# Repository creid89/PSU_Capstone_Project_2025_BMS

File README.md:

2025 PSU Senior Capstone Project

Battery Management System for PSU Student EPL (Engineering Prototyping Lab)

Members:
Cuauhtemoc Gomez Angeles <cuauh@pdx.edu>
Cody Reid <codreid@pdx.edu>
Fernando Custodio Calderon <fernan27@pdx.edu>
Tyler Tran <tytran@pdx.edu>
Daniel Anishchenko <danish2@pdx.edu>

Inudstry Sponsor: 
Edward Ivory <edivory@pdx.edu>

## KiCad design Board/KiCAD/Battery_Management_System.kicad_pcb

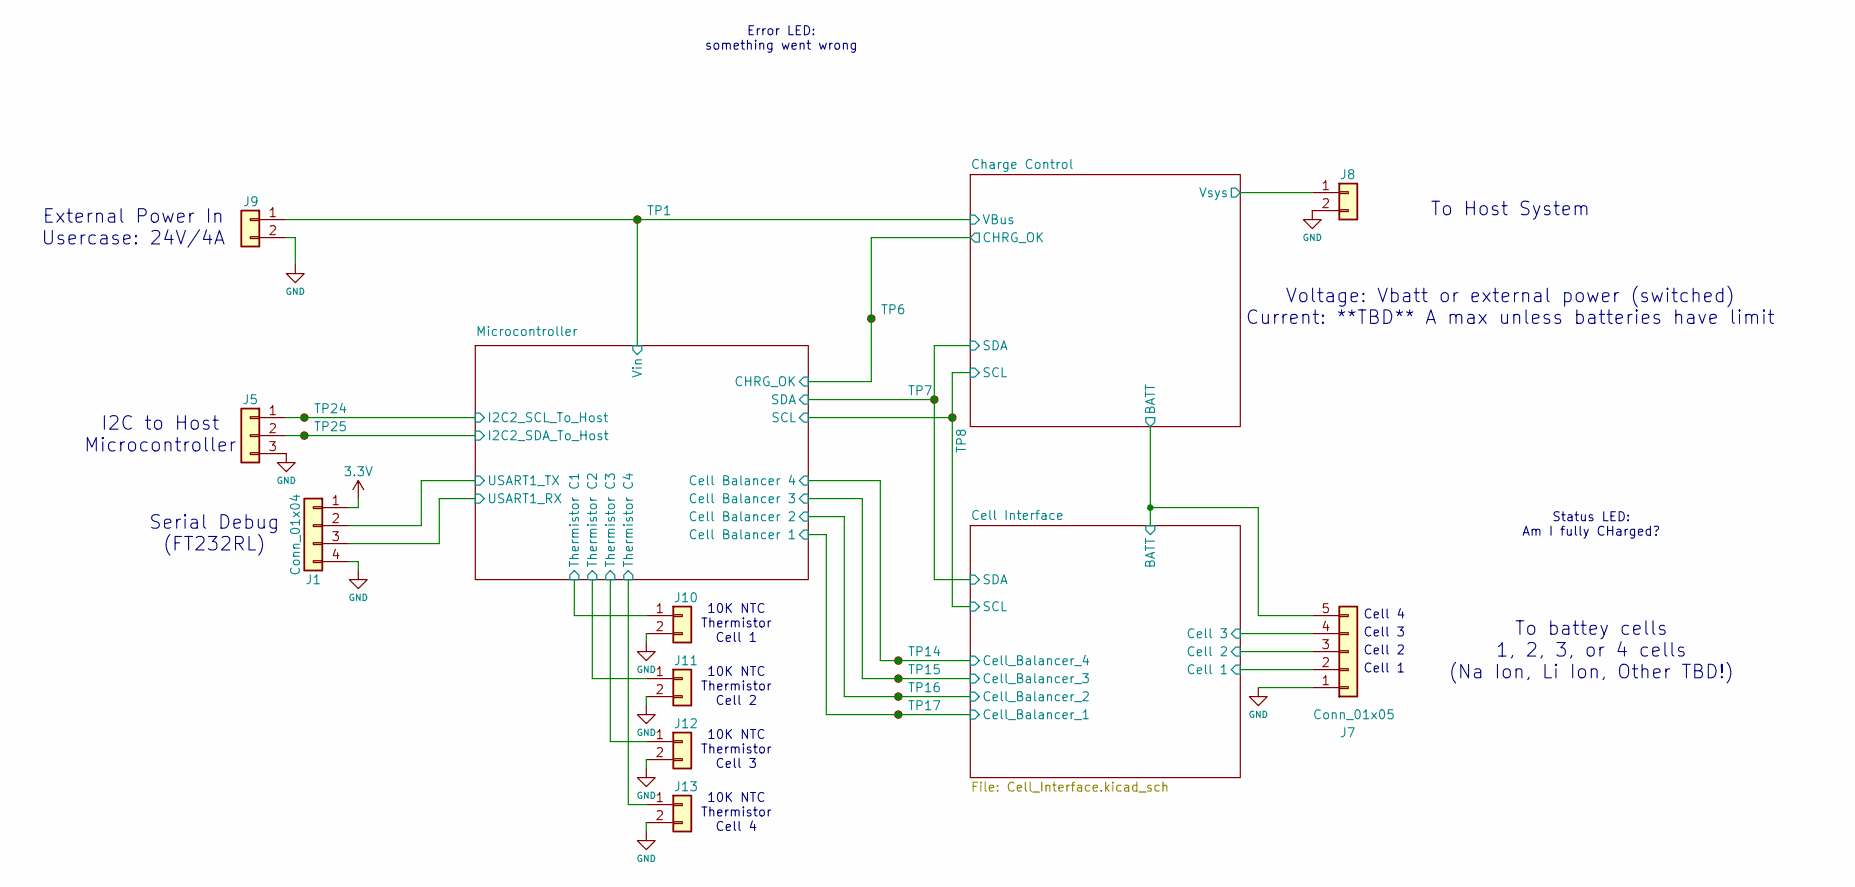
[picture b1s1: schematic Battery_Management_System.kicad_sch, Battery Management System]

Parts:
J1: Conn_01x04; PinHeader_1x04_P2.54mm_Vertical
J5: Conn_01x03; PinHeader_1x03_P2.54mm_Vertical; MPN 732-5316-ND
J7: Conn_01x05; PinHeader_1x05_P2.54mm_Vertical; MPN 732-5318-ND
J8, J9, J10, J11, J12, J13: Conn_01x02; PinHeader_1x02_P2.54mm_Vertical; MPN 5-146285-2-ND
TP1, TP6, TP7, TP8, TP14, TP15, TP16, TP17, TP24, TP25: TestPoint_Small; TestPoint_Pad_1.0x1.0mm

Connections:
3.3V: J1.1; also elsewhere on the board
/Cell Interface/BATT: J7.5; also elsewhere on the board
/Cell Interface/Cell 1: J7.2; also elsewhere on the board
/Cell Interface/Cell 2: J7.3; also elsewhere on the board
/Cell Interface/Cell 3: J7.4; also elsewhere on the board
/Cell Interface/Cell_Balancer_1: TP17.1; also elsewhere on the board
/Cell Interface/Cell_Balancer_2: TP16.1; also elsewhere on the board
/Cell Interface/Cell_Balancer_3: TP15.1; also elsewhere on the board
/Cell Interface/Cell_Balancer_4: TP14.1; also elsewhere on the board
/Cell Interface/SCL: TP8.1; also elsewhere on the board
/Cell Interface/SDA: TP7.1; also elsewhere on the board
/Charge Control/CHRG_OK: TP6.1; also elsewhere on the board
/Charge Control/VBus: J9.1, TP1.1; also elsewhere on the board
/Charge Control/Vsys: J8.1; also elsewhere on the board
/Microcontroller/I2C2_SCL_To_Host: J5.1, TP24.1; also elsewhere on the board
/Microcontroller/I2C2_SDA_To_Host: J5.2, TP25.1; also elsewhere on the board
/Microcontroller/Thermistor C1: J10.1; also elsewhere on the board
/Microcontroller/Thermistor C2: J11.1; also elsewhere on the board
/Microcontroller/Thermistor C3: J12.1; also elsewhere on the board
/Microcontroller/Thermistor C4: J13.1; also elsewhere on the board
/Microcontroller/USART1_RX: J1.3; also elsewhere on the board
/Microcontroller/USART1_TX: J1.2; also elsewhere on the board
GND: J1.4, J5.3, J7.1, J8.2, J9.2, J10.2, J11.2, J12.2, J13.2; also elsewhere on the board

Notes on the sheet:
Cell 3
I2C to Host Microcontroller
10K NTC Thermistor Cell 1
Cell 4
10K NTC Thermistor Cell 3
10K NTC Thermistor Cell 2
Error LED: something went wrong
To battey cells 1, 2, 3, or 4 cells (Na Ion, Li Ion, Other TBD!)
Cell 2
To Host System Voltage: Vbatt or external power (switched) Current: **TBD** A max unless batteries have limit
Serial Debug (FT232RL)
External Power In Usercase: 24V/4A
Cell 1
Status LED: Am I fully CHarged?
10K NTC Thermistor Cell 4

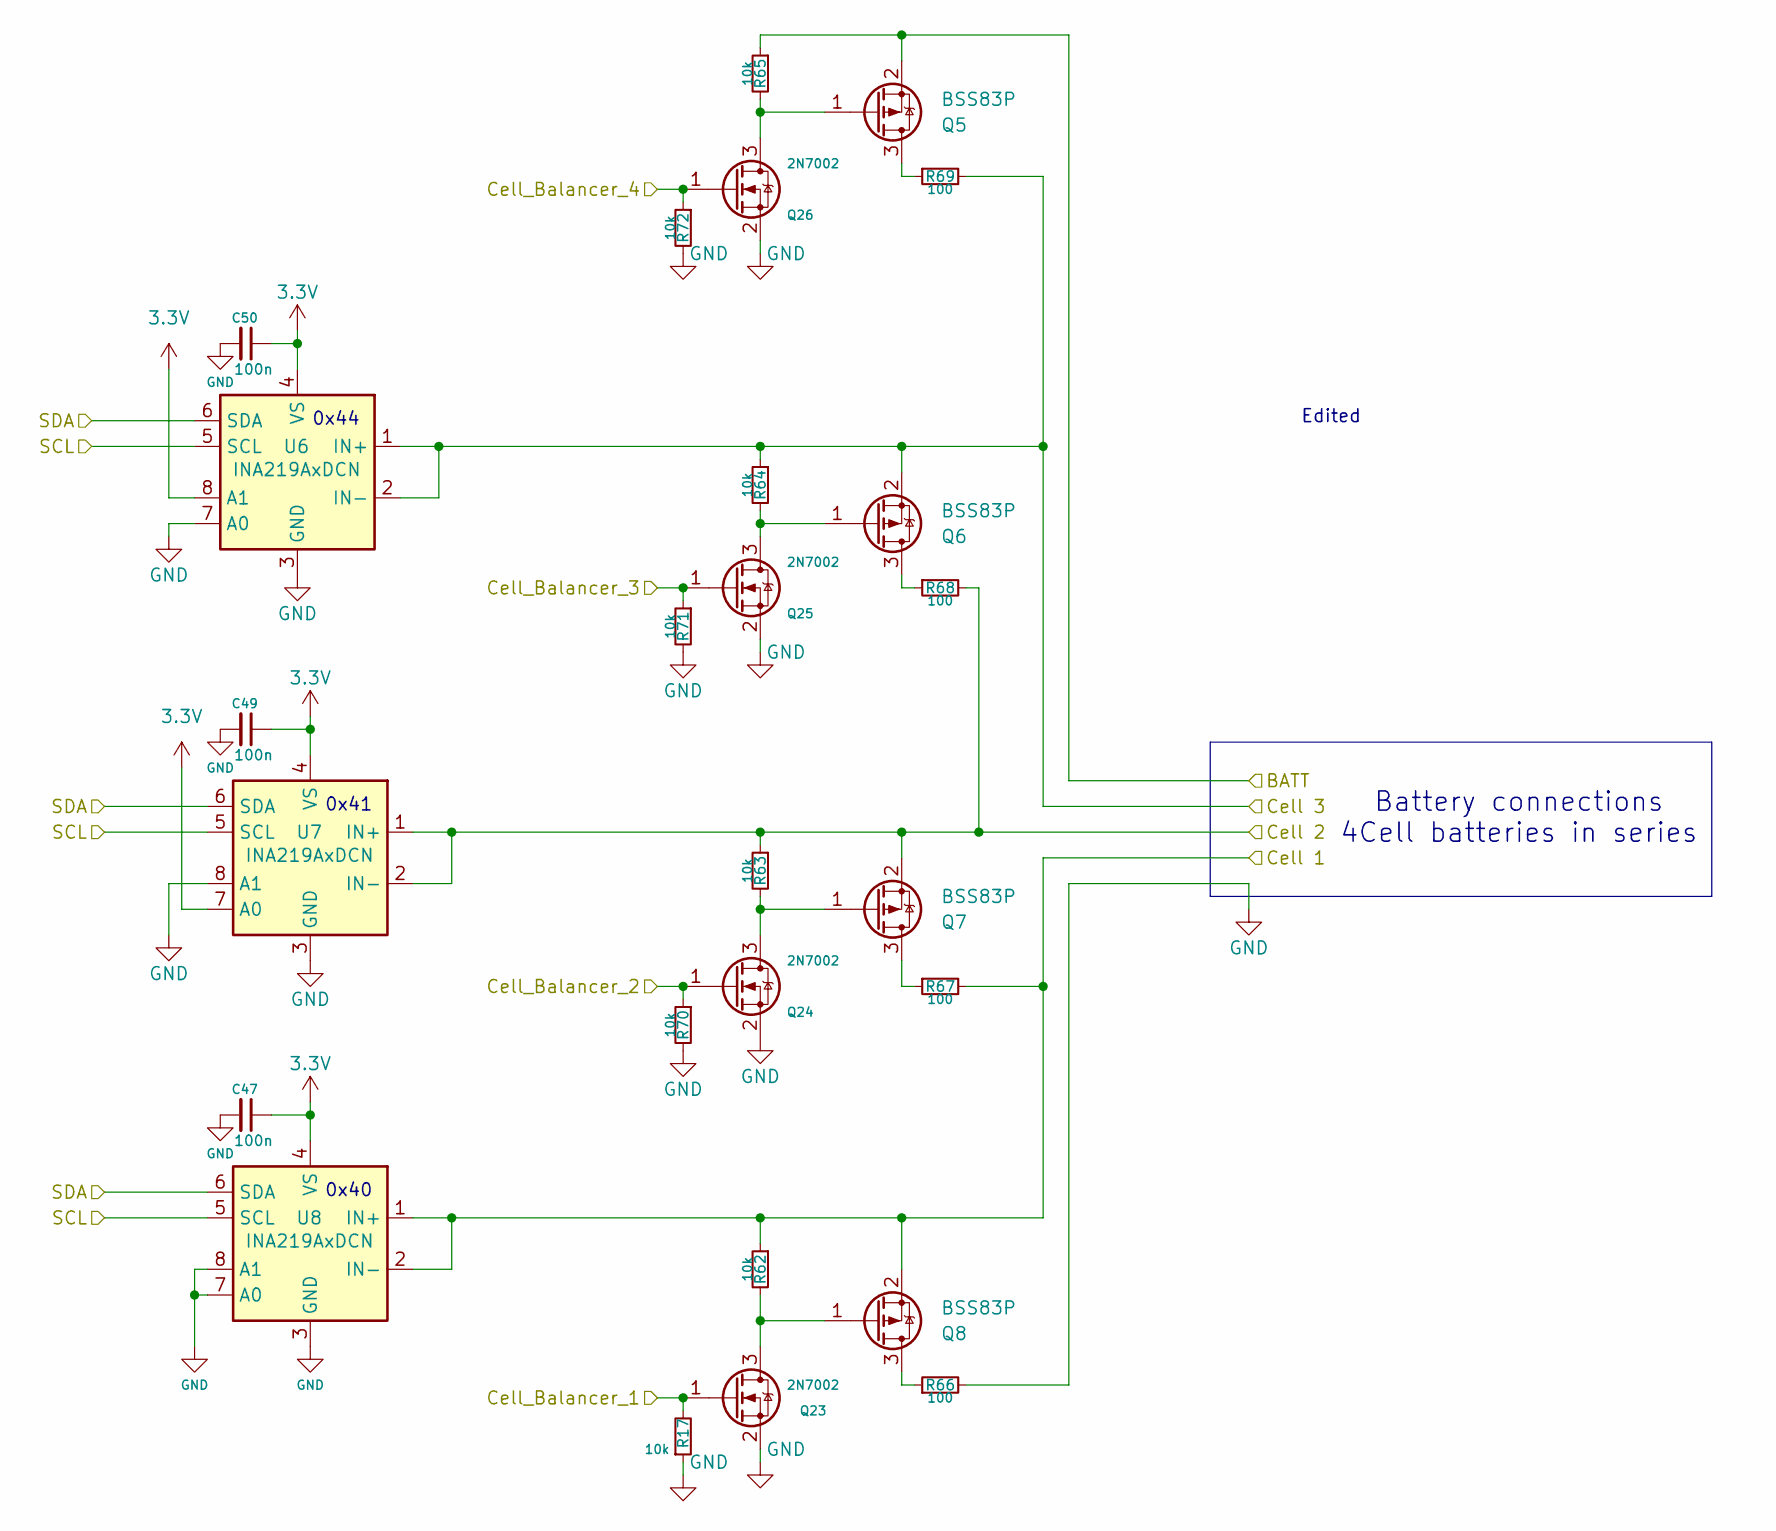
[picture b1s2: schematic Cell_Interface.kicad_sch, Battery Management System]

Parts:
C47, C49, C50: 100n; C_0603_1608Metric; MPN 1276-6720-1-ND
Q5, Q6, Q7, Q8: BSS83P; SOT-23; MPN BSS83PH6327XTSA1CT-ND
Q23, Q24, Q25, Q26: 2N7002; SOT-23; MPN 2N7002NCT-ND
R17, R62, R63, R64, R65, R70, R71, R72: 10k; R_0603_1608Metric; MPN RMCF0603FT10K0CT-ND
R66, R67, R68, R69: 100; R_1206_3216Metric; MPN RNCF1206TKY100RCT-ND
U6, U7, U8: INA219AxDCN; SOT-23-8; MPN 296-23770-1-ND

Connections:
3.3V: C47.1, C49.1, C50.1, U6.4 (VS), U6.8 (A1), U7.4 (VS), U7.7 (A0), U8.4 (VS); also elsewhere on the board
/Cell Interface/BATT: Q5.2 (S), R65.1; also elsewhere on the board
/Cell Interface/Cell 1: Q8.2 (S), R62.1, R67.2, U8.1 (IN+), U8.2 (IN-); also elsewhere on the board
/Cell Interface/Cell 2: Q7.2 (S), R63.1, R68.2, U7.1 (IN+), U7.2 (IN-); also elsewhere on the board
/Cell Interface/Cell 3: Q6.2 (S), R64.1, R69.2, U6.1 (IN+), U6.2 (IN-); also elsewhere on the board
/Cell Interface/Cell_Balancer_1: Q23.1 (G), R17.2; also elsewhere on the board
/Cell Interface/Cell_Balancer_2: Q24.1 (G), R70.1; also elsewhere on the board
/Cell Interface/Cell_Balancer_3: Q25.1 (G), R71.1; also elsewhere on the board
/Cell Interface/Cell_Balancer_4: Q26.1 (G), R72.1; also elsewhere on the board
/Cell Interface/SCL: U6.5 (SCL), U7.5 (SCL), U8.5 (SCL); also elsewhere on the board
/Cell Interface/SDA: U6.6 (SDA), U7.6 (SDA), U8.6 (SDA); also elsewhere on the board
GND: C47.2, C49.2, C50.2, Q23.2 (S), Q24.2 (S), Q25.2 (S), Q26.2 (S), R17.1, R66.2, R70.2, R71.2, R72.2, U6.3 (GND), U6.7 (A0), U7.3 (GND), U7.8 (A1), U8.3 (GND), U8.7 (A0), U8.8 (A1); also elsewhere on the board
unnamed: Q5.3 (D), R69.1
unnamed: Q6.3 (D), R68.1
unnamed: Q7.3 (D), R67.1
unnamed: Q8.3 (D), R66.1
unnamed: Q8.1 (G), Q23.3 (D), R62.2
unnamed: Q7.1 (G), Q24.3 (D), R63.2
unnamed: Q6.1 (G), Q25.3 (D), R64.2
unnamed: Q5.1 (G), Q26.3 (D), R65.2

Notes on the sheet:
0x44
Battery connections 4Cell batteries in series
Edited
0x40
0x41

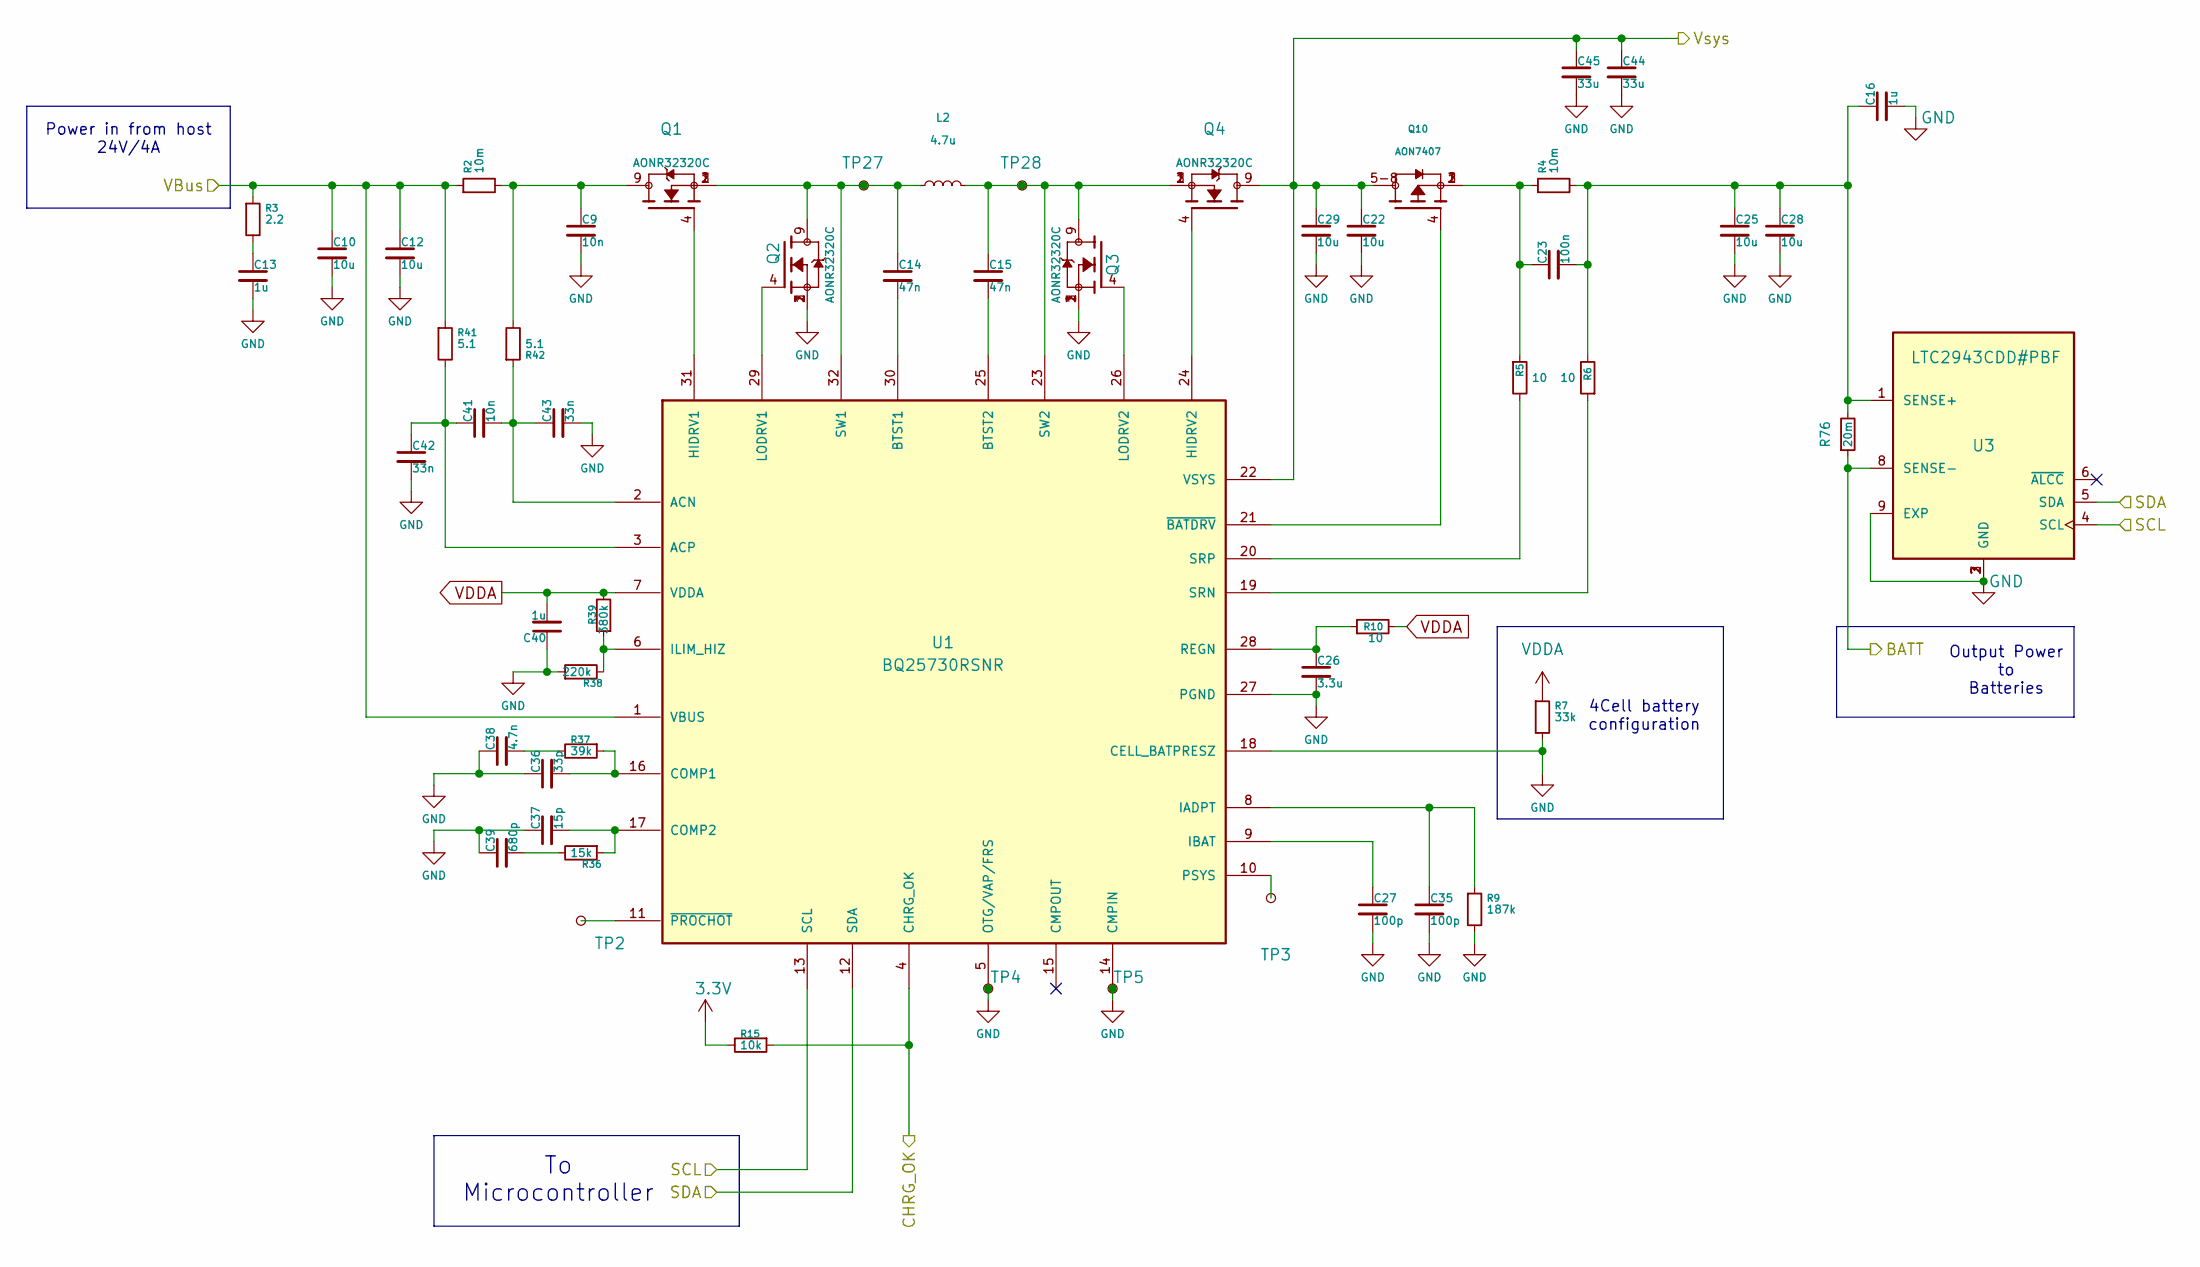
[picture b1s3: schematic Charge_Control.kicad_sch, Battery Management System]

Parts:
C9, C41: 10n; C_0603_1608Metric; MPN 490-3194-1-ND
C10, C12, C22, C25, C28, C29: 10u; C_1206_3216Metric; MPN 1276-1804-1-ND
C13, C16, C40: 1u; C_0603_1608Metric; MPN 1276-1946-1-ND
C14, C15: 47n; C_0603_1608Metric; MPN 490-4934-1-ND
C23: 100n; C_0603_1608Metric; MPN 1276-6720-1-ND
C26: 3.3u; C_0603_1608Metric; MPN 1276-1892-1-ND
C27, C35: 100p; C_0603_1608Metric; MPN 490-1427-1-ND
C36: 33p; C_0603_1608Metric; MPN 490-1415-1-ND
C37: 15p; C_0603_1608Metric; MPN 478-600S150JT250XT4KCT-ND
C38: 4.7n; C_0603_1608Metric; MPN 445-6912-1-ND
C39: 680p; C_0603_1608Metric; MPN 399-C0603C681F5GACTUCT-ND
C42, C43: 33n; C_0603_1608Metric; MPN 490-8025-1-ND
C44, C45: 33u; C_1206_3216Metric; MPN 490-1415-1-ND
L2: 4.7u; L_10.4x10.4_H4.8; MPN 495-1805-1-ND
Q1, Q2, Q3, Q4: AONR32320C; TRANS_AON7408; MPN 785-AONR32320CCT-ND
Q10: AON7407; TRANS_AON7407; MPN 785-1306-1-ND
R2, R4: 10m; R_1206_3216Metric; MPN CSR1206FK10L0CT-ND
R3: 2.2; R_1206_3216Metric
R5, R6, R10: 10; R_0603_1608Metric; MPN RMCF0603FT10R0CT-ND
R7: 33k; R_0603_1608Metric; MPN RMCF0603FT33K0CT-ND
R9: 187k; R_0603_1608Metric; MPN RMCF0603FT187KCT-ND
R15: 10k; R_0603_1608Metric; MPN RMCF0603FT10K0CT-ND
R36: 15k; R_0603_1608Metric; MPN RMCF0603FT15K0CT-ND
R37: 39k; R_0603_1608Metric; MPN RMCF0603JT39K0CT-ND
R38: 220k; R_0603_1608Metric; MPN RMCF0603FT220KCT-ND
R39: 380k; R_0603_1608Metric; MPN RMCF0603FT383KCT-ND
R41, R42: 5.1; R_0603_1608Metric; MPN RMCF0603FT5R10CT-ND
R76: 20m; R_1206_3216Metric; MPN CSR1206FK20L0CT-ND
TP2, TP3, TP4, TP5, TP27, TP28: TestPoint_Small; TestPoint_Pad_1.0x1.0mm
U1: BQ25730RSNR; IC_BQ25730RSNR; MPN BQ25730RSNR
U3: LTC2943CDD#PBF; MLF-8-1EP_3x3mm_P0.65mm_EP1.55x2.3mm; MPN LTC2943CDD#PBF

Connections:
3.3V: R15.2; also elsewhere on the board
/Cell Interface/BATT: R76.1, U3.8 (SENSE-); also elsewhere on the board
/Cell Interface/SCL: U1.13 (SCL), U3.4 (SCL); also elsewhere on the board
/Cell Interface/SDA: U1.12 (SDA), U3.5 (SDA); also elsewhere on the board
/Charge Control/CHRG_OK: R15.1, U1.4 (CHRG_OK); also elsewhere on the board
/Charge Control/VBus: C10.1, C12.1, R2.1, R3.1, R41.1, U1.1 (VBUS); also elsewhere on the board
/Charge Control/Vsys: C22.1, C29.1, C44.1, C45.1, Q4.9, Q10.5-8, U1.22 (VSYS); also elsewhere on the board
GND: C9.2, C10.2, C12.2, C13.2, C16.2, C22.2, C25.2, C26.2, C27.2, C28.2, C29.2, C35.2, C36.1, C37.1, C38.1, C39.1, C40.1, C42.2, C43.2, C44.2, C45.2, Q2.1, Q2.2, Q2.3, Q3.1, Q3.2, Q3.3, R7.2, R9.2, R38.1, TP4.1, TP5.1, U1.5 (OTG/VAP/FRS), U1.14 (CMPIN), U1.18 (CELL_BATPRESZ), U1.27 (PGND), U1.33, U1.34, U1.35, U1.36, U1.37, U1.38, U1.39, U1.40, U1.41, U1.42, U3.2 (GND), U3.3 (GND), U3.7 (GND), U3.9 (EXP); also elsewhere on the board
unnamed: C9.1, Q1.9, R2.2, R42.2
unnamed: C13.1, R3.2
unnamed: C23.1, Q10.1, Q10.2, Q10.3, R4.1, R5.1
unnamed: C38.2, R37.2
unnamed: C39.2, R36.2
unnamed: C41.2, C43.1, R42.1, U1.2 (ACN)
unnamed: C41.1, C42.1, R41.2, U1.3 (ACP)
unnamed: C14.2, U1.30 (BTST1)
unnamed: C15.2, U1.25 (BTST2)
unnamed: C36.2, R37.1, U1.16 (COMP1)
unnamed: C37.2, R36.1, U1.17 (COMP2)
unnamed: Q1.4, U1.31 (HIDRV1)
unnamed: Q4.4, U1.24 (HIDRV2)
unnamed: C35.1, R9.1, U1.8 (IADPT)
unnamed: C27.1, U1.9 (IBAT)
unnamed: R38.2, R39.1, U1.6 (ILIM_HIZ)
unnamed: Q2.4, U1.29 (LODRV1)
unnamed: Q3.4, U1.26 (LODRV2)
unnamed: TP3.1, U1.10 (PSYS)
unnamed: C26.1, R10.1, U1.28 (REGN)
unnamed: R6.1, U1.19 (SRN)
unnamed: R5.2, U1.20 (SRP)
unnamed: C14.1, L2.1, Q1.1, Q1.2, Q1.3, Q2.9, TP27.1, U1.32 (SW1)
unnamed: C15.1, L2.2, Q3.9, Q4.1, Q4.2, Q4.3, TP28.1, U1.23 (SW2)
unnamed: Q10.4, U1.21 (~BATDRV)
unnamed: TP2.1, U1.11 (~PROCHOT)
unnamed: C16.1, C23.2, C25.1, C28.1, R4.2, R6.2, R76.2, U3.1 (SENSE+)
VDDA: C40.2, R7.1, R10.2, R39.2, U1.7 (VDDA)

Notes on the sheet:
4Cell battery configuration
To Microcontroller
Power in from host 24V/4A
Output Power to Batteries

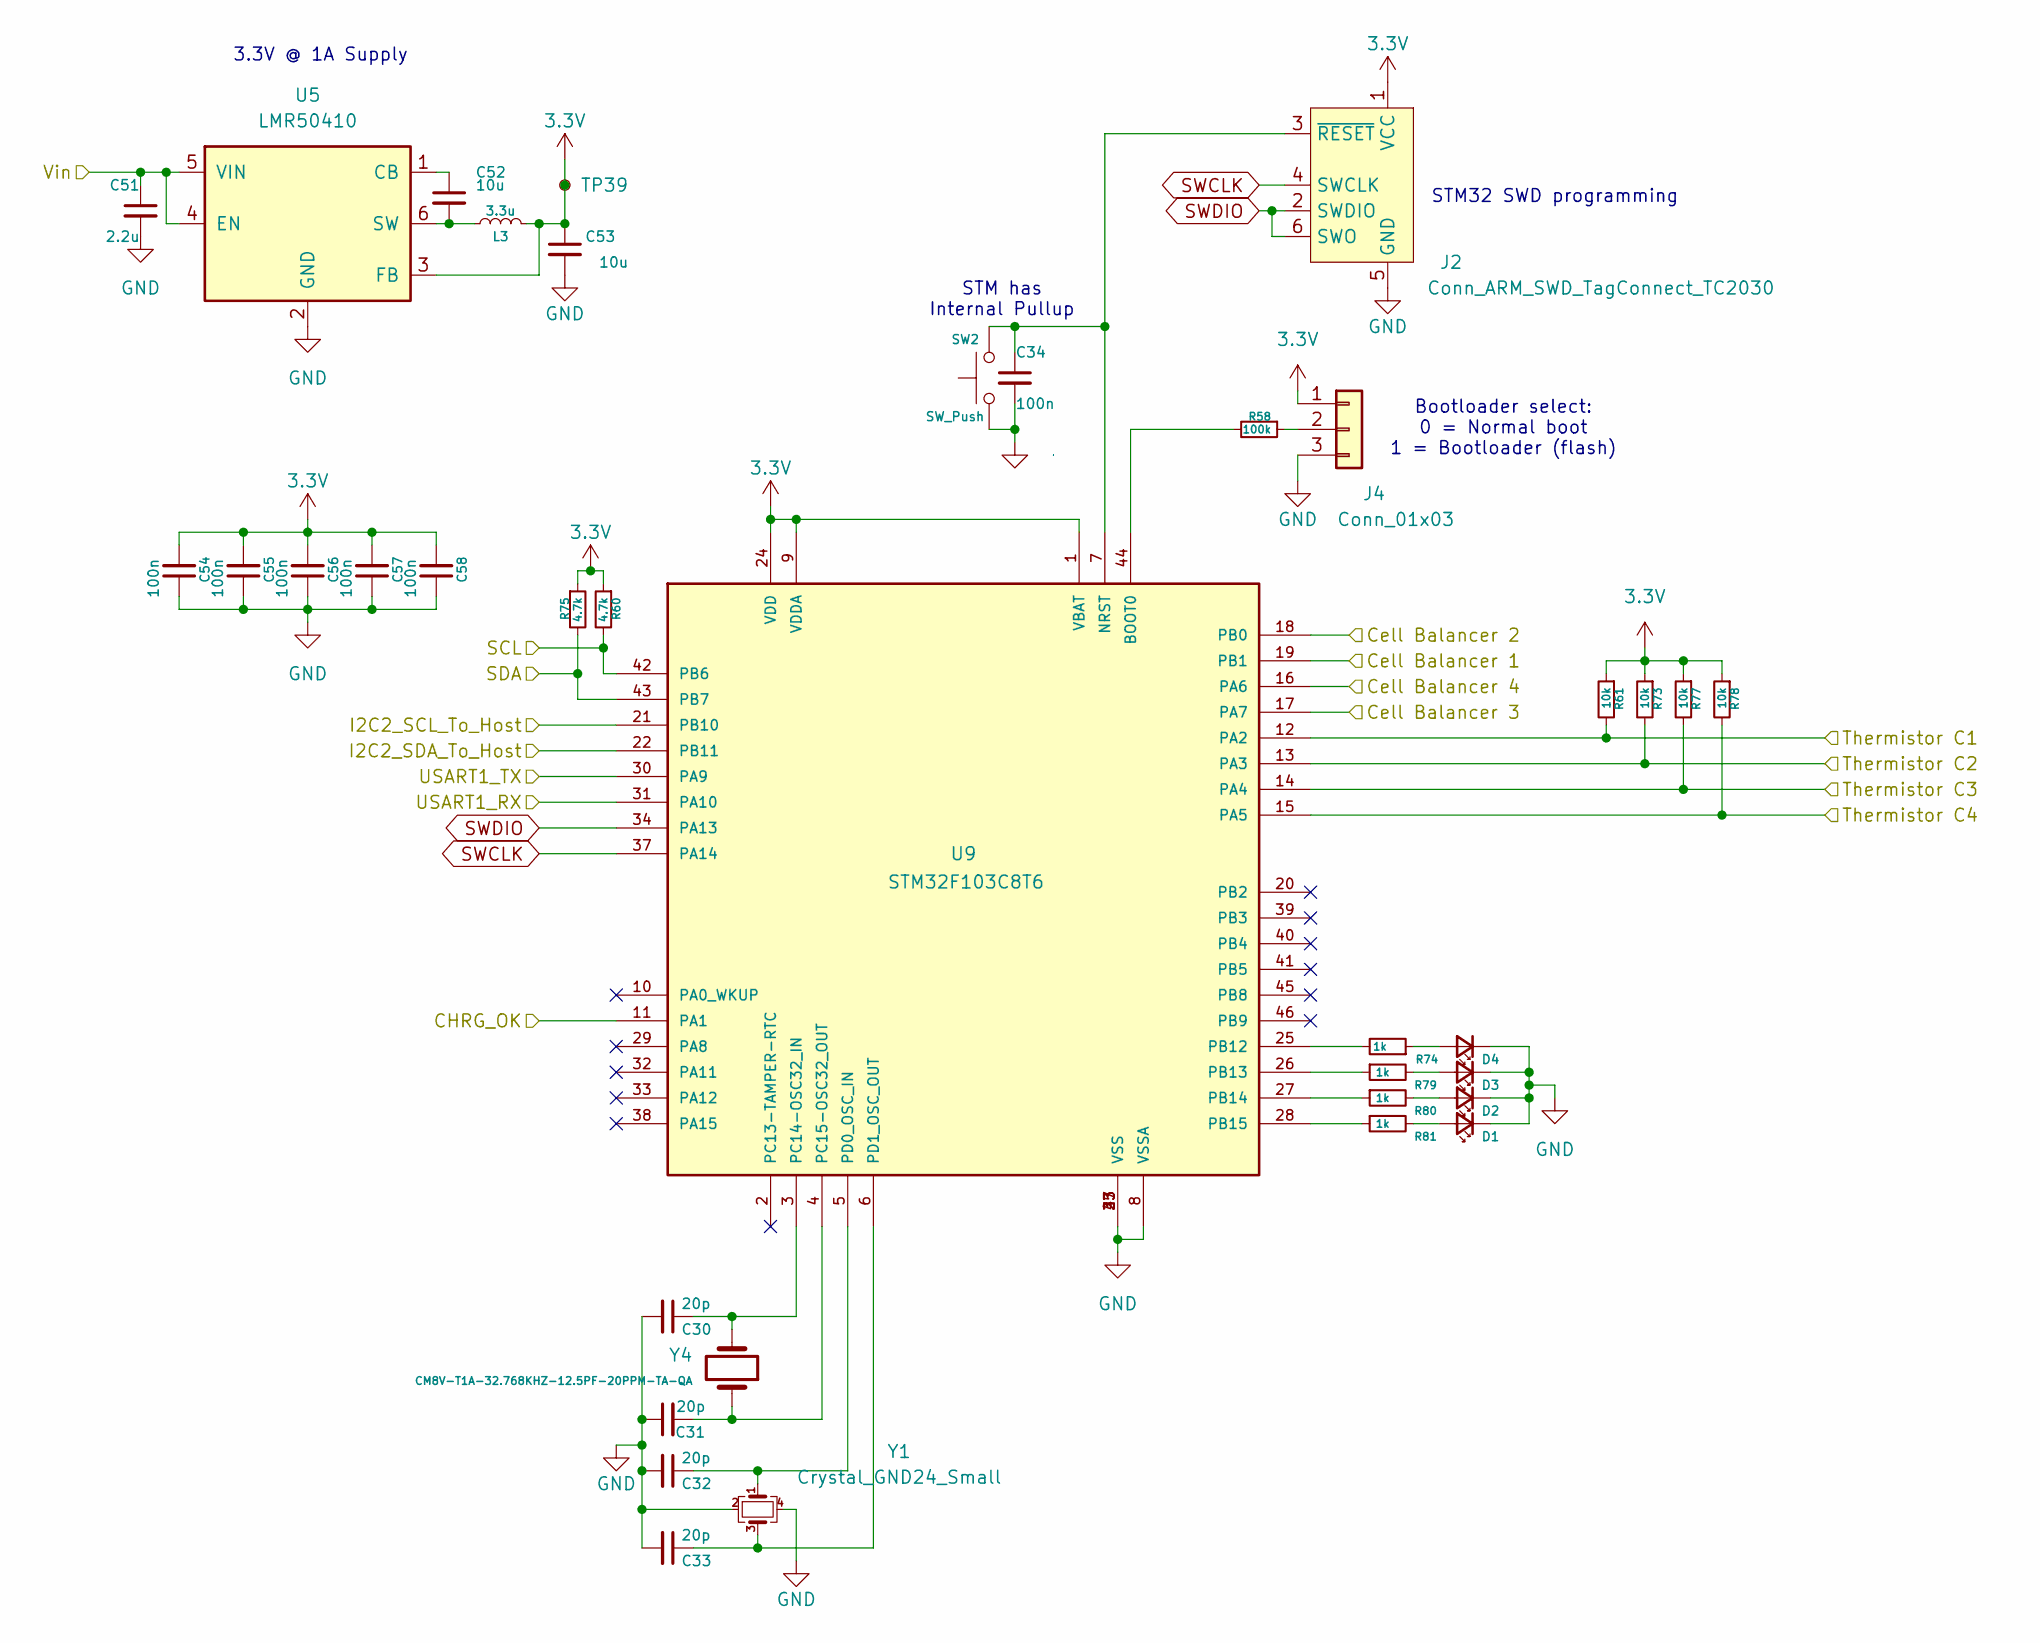
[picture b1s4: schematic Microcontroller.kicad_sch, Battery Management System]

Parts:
C30, C31, C32, C33: 20p; C_0603_1608Metric; MPN 478-600S200FT250XT4KCT-ND
C34, C54, C55, C56, C57, C58: 100n; C_0603_1608Metric; MPN 1276-6720-1-ND
C51: 2.2u; C_1206_3216Metric; MPN 587-2909-1-ND
C52, C53: 10u; C_1206_3216Metric; MPN 1276-1804-1-ND
D1, D2, D3, D4: LED_Small; LED_0603_1608Metric
J2: Conn_ARM_SWD_TagConnect_TC2030; Tag-Connect_TC2030-IDC-NL_2x03_P1.27mm_Vertical; MPN TC2030-CTX-ND
J4: Conn_01x03; PinHeader_1x03_P2.54mm_Vertical; MPN 732-5316-ND
L3: 3.3u; L_1008_2520Metric_Pad1.43x2.20mm_HandSolder; MPN 587-3227-1-ND
R58: 100k; R_0603_1608Metric; MPN RMCF0603FT100KCT-ND
R60, R75: 4.7k; R_0603_1608Metric; MPN RMCF0603FT4K70CT-ND
R61, R73, R77, R78: 10k; R_0603_1608Metric; MPN RMCF0603FT10K0CT-ND
R74, R79, R80, R81: 1k; R_0603_1608Metric; MPN RMCF0603FT10K0CT-ND
SW2: SW_Push; SW_Push_SPST_NO_Alps_SKRK; MPN CKN12220-1-ND
TP39: TestPoint_Small; TestPoint_Pad_1.0x1.0mm
U5: LMR50410; SOT-23-6; MPN 296-LMR50410XFDBVRCT-ND
U9: STM32F103C8T6; QFP50P900X900X160-48N; MPN STM32F103C8T6
Y1: Crystal_GND24_Small; Crystal_SMD_TXC_7M-4Pin_3.2x2.5mm; MPN 7V-8.000MDDQ-T
Y4: CM8V-T1A-32.768KHZ-12.5PF-20PPM-TA-QA; XTAL_CM8V-T1A-32.768KHZ-12.5PF-20PPM-TA-QA; MPN CM8V-T1A-32.768KHZ-12.5PF-20PPM-TA-QA

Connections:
3.3V: C53.1, C54.2, C55.2, C56.2, C57.2, C58.2, J2.1 (VCC), J4.1, L3.2, R60.1, R61.1, R73.1, R75.1, R77.1, R78.1, TP39.1, U5.3 (FB), U9.1 (VBAT), U9.9 (VDDA), U9.24 (VDD), U9.36 (VDD), U9.48 (VDD); also elsewhere on the board
/Cell Interface/Cell_Balancer_1: U9.19 (PB1); also elsewhere on the board
/Cell Interface/Cell_Balancer_2: U9.18 (PB0); also elsewhere on the board
/Cell Interface/Cell_Balancer_3: U9.17 (PA7); also elsewhere on the board
/Cell Interface/Cell_Balancer_4: U9.16 (PA6); also elsewhere on the board
/Cell Interface/SCL: R60.2, U9.42 (PB6); also elsewhere on the board
/Cell Interface/SDA: R75.2, U9.43 (PB7); also elsewhere on the board
/Charge Control/CHRG_OK: U9.11 (PA1); also elsewhere on the board
/Charge Control/VBus: C51.1, U5.4 (EN), U5.5 (VIN); also elsewhere on the board
/Microcontroller/I2C2_SCL_To_Host: U9.21 (PB10); also elsewhere on the board
/Microcontroller/I2C2_SDA_To_Host: U9.22 (PB11); also elsewhere on the board
/Microcontroller/Thermistor C1: R61.2, U9.12 (PA2); also elsewhere on the board
/Microcontroller/Thermistor C2: R73.2, U9.13 (PA3); also elsewhere on the board
/Microcontroller/Thermistor C3: R77.2, U9.14 (PA4); also elsewhere on the board
/Microcontroller/Thermistor C4: R78.2, U9.15 (PA5); also elsewhere on the board
/Microcontroller/USART1_RX: U9.31 (PA10); also elsewhere on the board
/Microcontroller/USART1_TX: U9.30 (PA9); also elsewhere on the board
GND: C30.2, C31.1, C32.2, C33.2, C34.2, C51.2, C53.2, C54.1, C55.1, C56.1, C57.1, C58.1, D1.1 (K), D2.1 (K), D3.1 (K), D4.1 (K), J2.5 (GND), J4.3, SW2.1, U5.2 (GND), U9.8 (VSSA), U9.23 (VSS), U9.35 (VSS), U9.47 (VSS), Y1.2, Y1.4; also elsewhere on the board
unnamed: D1.2 (A), R81.2
unnamed: D2.2 (A), R80.2
unnamed: D3.2 (A), R79.2
unnamed: D4.2 (A), R74.1
unnamed: C34.1, J2.3 (~RESET), SW2.2, U9.7 (NRST)
unnamed: J4.2, R58.1
unnamed: C52.1, U5.1 (CB)
unnamed: C52.2, L3.1, U5.6 (SW)
unnamed: R58.2, U9.44 (BOOT0)
unnamed: R74.2, U9.25 (PB12)
unnamed: R79.1, U9.26 (PB13)
unnamed: R80.1, U9.27 (PB14)
unnamed: R81.1, U9.28 (PB15)
unnamed: C30.1, U9.3 (PC14-OSC32_IN), Y4.2
unnamed: C31.2, U9.4 (PC15-OSC32_OUT), Y4.1
unnamed: C32.1, U9.5 (PD0_OSC_IN), Y1.1
unnamed: C33.1, U9.6 (PD1_OSC_OUT), Y1.3
SWCLK: J2.4 (SWCLK), U9.37 (PA14)
SWDIO: J2.2 (SWDIO), J2.6 (SWO), U9.34 (PA13)

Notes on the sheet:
STM32 SWD programming
3.3V @ 1A Supply
Bootloader select: 0 = Normal boot 1 = Bootloader (flash)
STM has Internal Pullup

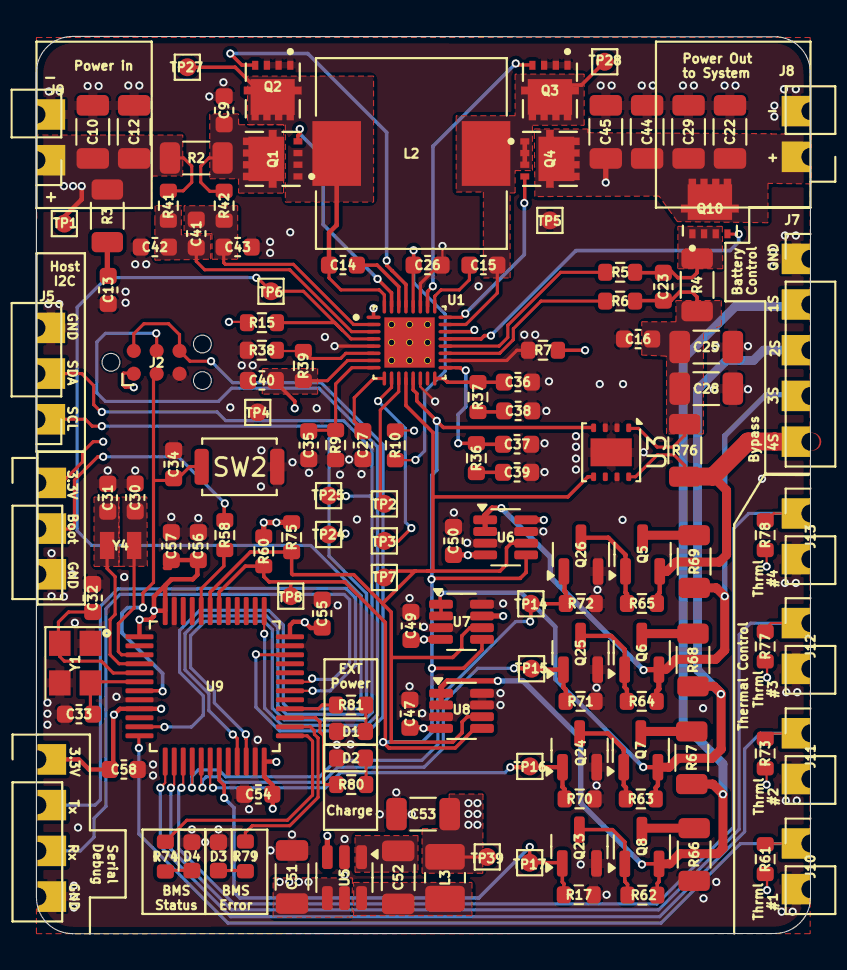
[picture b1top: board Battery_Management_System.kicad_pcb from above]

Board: 4 copper layers, 43.0 x 49.8 mm, 137 parts (0 on the bottom side), 78 nets.

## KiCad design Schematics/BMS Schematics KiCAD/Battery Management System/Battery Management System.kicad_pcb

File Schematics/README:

This folder contains the schematic designs and associated files for the hardware or electronics project. These schematics are essential for understanding the circuit design and the layout of the project.

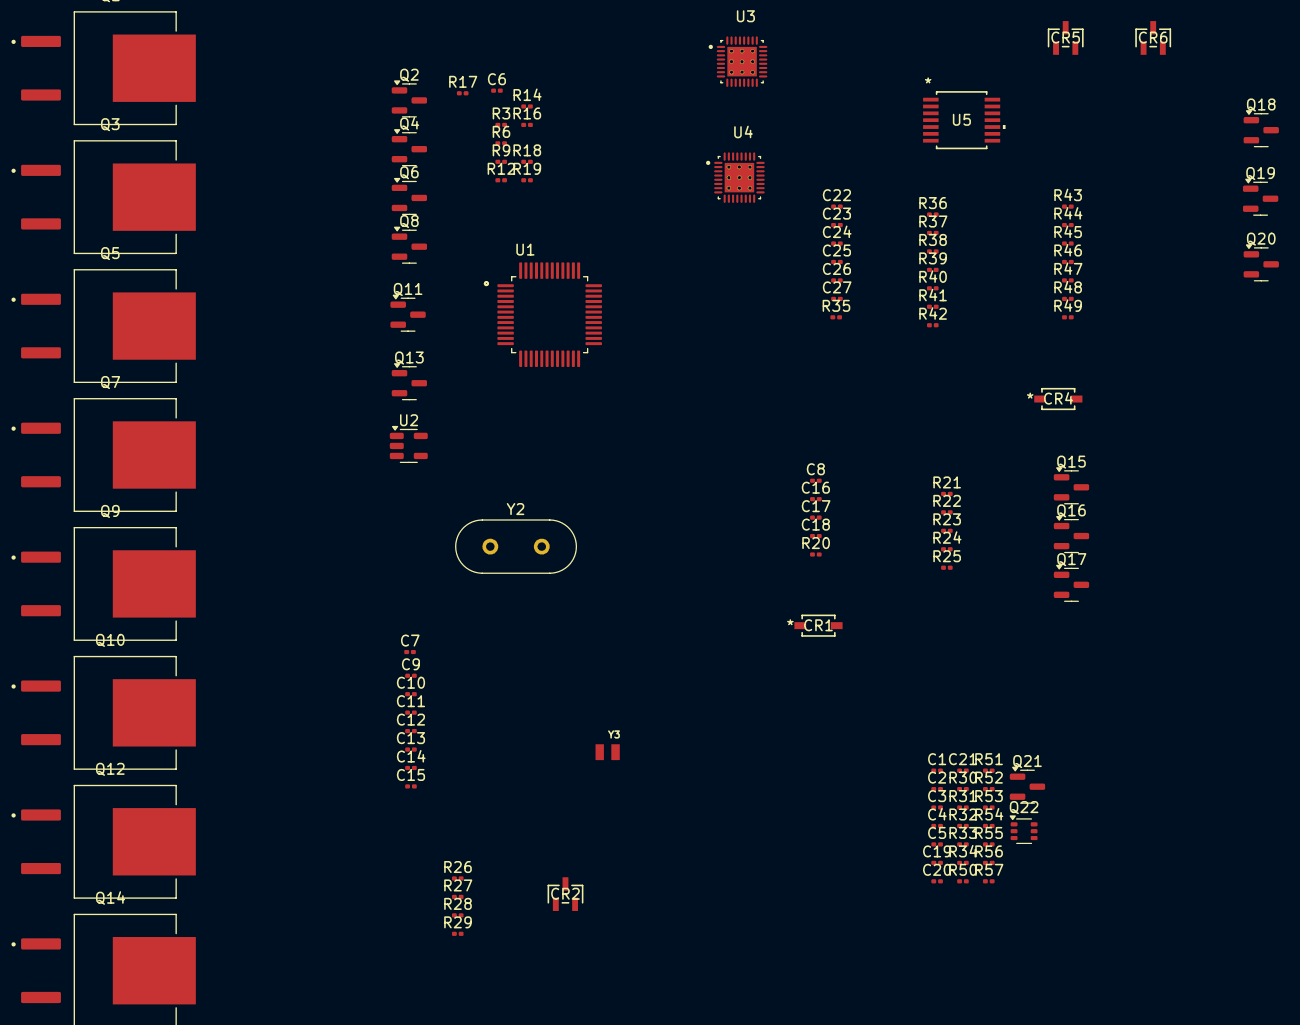
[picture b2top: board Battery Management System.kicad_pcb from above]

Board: 2 copper layers, 108 parts (0 on the bottom side), 78 nets, no tracks yet.

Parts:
C1, C2, C3, C4, C5, C8, C17, C18, C21: C; R_0201_0603Metric
C6, C7, C22, C23, C24: 1uF; C_0201_0603Metric
C9: 22nF; C_0201_0603Metric
C10: 10uF; C_0201_0603Metric
C11, C25, C26, C27: 0.1uF; C_0201_0603Metric
C12, C13, C14, C15: 20pF; C_0201_0603Metric
C16: C; C_0201_0603Metric
C19: 33p; R_0201_0603Metric
C20: 15p; R_0201_0603Metric
CR1, CR4: BZT52C5V6T-7; ZDO_SOD123_DIO
CR2, CR5, CR6: AZ23C5V6-7-F; DIODE3_AZ23C5V6-7-F_DIO
Q1, Q3, Q5, Q7, Q9, Q10, Q12, Q14: IRF9540NSTRLPBF; DPAK254P1524X483-4_3N
Q2, Q4, Q6, Q8, Q11, Q13, Q15, Q16, Q17, Q18, Q20, Q21: 2N7002; SOT-23
Q19: BSS84; SOT-23
Q22: BSD235C; SOT-363_SC-70-6
R3, R6, R9, R12, R14, R16, R35, R36, R37, R38, R39, R40, R41, R42, R43, R44, R45, R46, R47, R48, R49: R_Small; R_0201_0603Metric
R17, R34, R50, R51, R52, R54: 10k; R_0201_0603Metric
R18, R19: 100k; R_0201_0603Metric
R20, R22, R24, R25, R26, R27, R29, R55, R56, R57: R; R_0201_0603Metric
R21: 10; R_0201_0603Metric
R23: 220k; R_0201_0603Metric
R28: 380k; R_0201_0603Metric
R30: 40.2k; R_0201_0603Metric
R31: 15k; R_0201_0603Metric
R32, R33: 1k; R_0201_0603Metric
R53: 30k; R_0201_0603Metric
U1: STM32F103C8T6; QFP50P900X900X160-48N
U2: RT9193-33GB; SOT-23-5
U3, U4: BQ25730RSNR; IC_BQ25730RSNR
U5: BQ34Z100PWR-R2; PW14_TEX
Y2: 8MHz; Crystal_HC49-4H_Vertical
Y3: CM8V-T1A-32.768KHZ-12.5PF-20PPM-TA-QA; XTAL_CM8V-T1A-32.768KHZ-12.5PF-20PPM-TA-QA

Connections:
3.3V: C10.1, C11.1, R17.2, U1.9 (VDDA), U1.24 (VDD), U1.36 (VDD), U1.48 (VDD), U2.5 (VOUT)
5V: C7.1, U2.1 (VIN), U2.3 (EN)
Boot0: R18.2, U1.44 (BOOT0)
Boot1: R19.1, U1.20 (PB2)
Cell Balancer 1: Q2.1 (G), R3.2, U1.19 (PB1)
Cell Balancer 2: Q4.1 (G), R6.2, U1.18 (PB0)
Cell Balancer 3: Q6.1 (G), R9.2, U1.17 (PA7)
Cell Balancer 4: Q8.1 (G), R12.2, U1.16 (PA6)
GND: C4.1, C6.2, C7.2, C8.1, C9.2, C10.2, C11.2, C12.2, C13.1, C14.2, C15.2, C16.2, C17.2, C18.2, C19.2, C20.2, C21.2, C22.2, C23.2, C24.2, C25.1, C26.1, CR1.2, CR2.3, CR4.2, CR5.3, CR6.2, Q2.2 (S), Q4.2 (S), Q6.2 (S), Q8.2 (S), Q11.2 (S), Q13.2 (S), Q16.2 (S), Q17.2 (S), Q20.2 (S), R3.1, R6.1, R9.1, R12.1, R14.1, R16.1, R20.2, R22.2, R23.1, R25.2, R33.1, R39.2, R53.2, U1.8 (VSSA), U1.23 (VSS), U1.35 (VSS), U1.47 (VSS), U2.2 (GND), U3.27 (PGND), U3.33 (EXP), U5.8 (VSS)
unnamed: C1.1, R56.2, R57.1
unnamed: C1.2, R55.1, R56.1
unnamed: C18.1, R30.2
unnamed: C21.1, R31.2
unnamed: CR5.1, R46.1, R48.2
unnamed: CR5.2, R45.2, R47.1
unnamed: CR6.1, R44.2, R49.1
unnamed: Q1.1, Q2.3 (D)
unnamed: Q3.1, Q4.3 (D)
unnamed: Q5.1, Q6.3 (D)
unnamed: Q7.1, Q8.3 (D)
unnamed: Q9.4, Q10.4
unnamed: Q9.1, Q10.1, Q11.3 (D)
unnamed: Q11.1 (G), R14.2
unnamed: Q12.4, Q14.4
unnamed: Q12.1, Q13.3 (D), Q14.1
unnamed: Q13.1 (G), R16.2
unnamed: C2.1, Q15.3 (D), Q16.3 (D), U3.32 (SW1)
unnamed: Q15.1 (G), U3.31 (HIDRV1)
unnamed: Q15.2 (S), R27.2, R29.1
unnamed: CR1.1, Q16.1 (G), U3.29 (LODRV1)
unnamed: C3.1, Q17.3 (D), Q21.2 (S), U3.23 (SW2)
unnamed: Q17.1 (G), U3.26 (LODRV2)
unnamed: CR4.1, Q18.1 (G), R35.1
unnamed: Q19.3 (D), R38.2
unnamed: Q19.1 (G), R36.1, R37.2
unnamed: Q19.2 (S), R35.2, R36.2
unnamed: Q20.3 (D), R37.1
unnamed: Q20.1 (G), U5.2 (VEN)
unnamed: Q21.3 (D), U3.22 (VSYS)
unnamed: Q21.1 (G), U3.24 (HIDRV2)
unnamed: R34.2, R50.2, R51.2, R52.2
unnamed: R41.1, R42.2
unnamed: R41.2, R43.2
unnamed: C9.1, U2.4 (BP)
unnamed: C5.1, C8.2, R29.2, U3.2 (ACN)
unnamed: C5.2, R26.2, U3.3 (ACP)
unnamed: C2.2, U3.30 (BTST1)
unnamed: C3.2, U3.25 (BTST2)
unnamed: R24.2, R25.1, U3.18 (CELL_BATPRESZ)
unnamed: R51.1, U3.4 (CHRG_OK)
unnamed: R32.2, R33.2, U3.14 (CMPIN)
unnamed: R52.1, U3.15 (CMPOUT)
unnamed: C19.1, R30.1, U3.16 (COMP1)
unnamed: C20.1, R31.1, U3.17 (COMP2)
unnamed: C17.1, R22.1, U3.8 (IADPT)
unnamed: R20.1, U3.9 (IBAT)
unnamed: R23.2, R28.1, U3.6 (ILIM_HIZ)
unnamed: R53.1, U3.10 (PSYS)
unnamed: C4.2, U3.28 (REGN)
unnamed: R50.1, U3.13 (SCL)
unnamed: R34.1, U3.12 (SDA)
unnamed: R55.2, U3.19 (SRN)
unnamed: R57.2, U3.20 (SRP)
unnamed: C16.1, R21.2, R28.2, U3.7 (VDDA)
unnamed: R54.1, U3.11 (~PROCHOT)
unnamed: C23.1, R38.1, R39.1, U5.4 (BAT)
unnamed: R45.1, U5.14 (P3/SDA)
unnamed: R46.2, U5.13 (P4/SCL)
unnamed: R44.1, U5.12 (P5/HDQ)
unnamed: C26.2, C27.1, R43.1, U5.10 (SRN)
unnamed: C25.2, C27.2, R42.1, U5.9 (SRP)
PC14-OSC32_IN: C12.1, U1.3 (PC14-OSC32_IN), Y3.2
PC15-OSC32_OUT: C13.2, Y3.1
PD0-OSC_IN: C14.1, U1.5 (PD0_OSC_IN), Y2.2
PD1-OSC_OUT: C15.1, Y2.1
REG25: C22.1, C24.1, Q18.2 (S), R40.2, U5.5 (CE), U5.6 (REGIN), U5.7 (REG25)
Reset: C6.1, R17.1, U1.7 (NRST)
VBUS: R26.1, R27.1, U3.1 (VBUS)
